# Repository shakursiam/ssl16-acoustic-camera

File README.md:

# SSL-16 — 16-Channel Acoustic Sound Source Localization Board (Lab Prototype, Rev A)

The **SSL-16** is an integrated 16-channel acoustic camera system engineered for real-time sound source localization (SSL) and acoustic beamforming, designed for downward-looking deployment to localize vehicle honking and characterize acoustic profiles in dense urban traffic environments (such as Dhaka, Bangladesh). The hardware integrates **16 Infineon IM73A135 differential analog MEMS microphones** arranged in a non-uniform Vogel (sunflower) spiral layout within an 80 mm radius aperture ($D = 160\,\text{mm}$), digitized synchronously by **four Texas Instruments TLV320ADC5140 4-channel ADCs** over a shared, daisy-chained 16-channel TDM bus into an **Espressif ESP32-S3-WROOM-1-N8R8** dual-core microcontroller with 8 MB Octal PSRAM.

---

## 3D Renders (Rev A)

<p align="center">
  <em>Figure 1: (Left) Top acoustic face with 16 sunflower sound entry ports. (Right) Bottom surface hosting all SMD components, differential routing, and ground flood.</em>
</p>

---

## Key Specifications

| Parameter | Specification / Value | Notes |
|---|---|---|
| **Microphone Array** | 16 × Infineon IM73A135V01XTSA1 (`MK1`–`MK16`) | Analog, differential, bottom-port, 73 dB(A) SNR, 135 dB SPL AOP |
| **Array Geometry** | Vogel / Sunflower spiral ($R = 80\,\text{mm}$ aperture) | Eliminates spatial aliasing up to 6 kHz; bottom-port through 0.8 mm NPTH holes |
| **Audio ADCs** | 4 × TI TLV320ADC5140 (`U1`–`U4`) | 4 differential analog inputs each; QFN-24 with 9 thermal vias per pad |
| **Sample Format** | TDM, 16 slots × 16 bits, $f_s = 48\,\text{kHz}$ | $\text{BCLK} = 12.288\,\text{MHz}$ (256 BCLK cycles per frame) |
| **Master Clock (MCLK)** | 24.576 MHz 3.3V CMOS XO (Abracon ASE-24.576MHZ-LC-T, `Y1`) | Directly feeds `U4` (`GPIO1`); `U4` acts as sole TDM Controller |
| **Clock Fan-Out Buffer** | TI LMK1C1104 (`U10`), 1:4 LVCMOS Buffer | Skew $< 30\,\text{ps}$; buffered BCLK feeds `U1`–`U3` and ESP32 `IO6` via 33 Ω damping resistors |
| **Microcontroller (MCU)**| ESP32-S3-WROOM-1-N8R8 (`U5`) | Dual-core Xtensa LX7 @ 240 MHz, 8 MB Flash, 8 MB Octal PSRAM, native USB-Serial/JTAG |
| **External Storage** | MicroSD socket (Molex 104031-0811, `J601`) | Native 4-bit SDMMC bus (`IO4`, `IO5`, `IO15`, `IO16`, `IO18`, `IO21`) |
| **Power Inputs** | 12 V DC barrel jack (`J8`) or USB-C 5 V (`J2`) | Automatic ideal-diode OR-ing ($Q_1$ P-MOSFET + $D_1$ Schottky) into `VSYS` |
| **Power Regulators** | XL2596S-5.0 (5V buck), AP2112K-3.3 (3V3 digital), TPS7A2033 (3V3A clean analog) | Unified continuous GND plane (no split analog ground) |
| **PCB Dimensions** | 230 mm × 170 mm, 4 layers, 1.6 mm nominal thickness | Stack-up: **JLCPCB JLC04161H-7628**; all 193 SMD components on bottom side |
| **Usable Acoustic Band**| **~1.5 kHz to 6.0 kHz** | Broad mainlobe below 1.5 kHz; zero grating lobes up to 6.0 kHz |

---

## System Architecture

```mermaid
flowchart TD
    subgraph FrontEnd ["Acoustic Array & Transducers"]
        direction LR
        MIC1["MK2, MK7, MK10, MK15<br/>(4× IM73A135 Diff)"]
        MIC2["MK1, MK4, MK9, MK12<br/>(4× IM73A135 Diff)"]
        MIC3["MK3, MK6, MK11, MK14<br/>(4× IM73A135 Diff)"]
        MIC4["MK5, MK8, MK13, MK16<br/>(4× IM73A135 Diff)"]
    end

    subgraph MasterClock ["Master Clock Source"]
        Y1["Abracon 24.576 MHz XO<br/>(ASE-24.576MHZ-LC-T)"]
        R22["R22 (33 Ω)"]
        Y1 --> R22
    end

    subgraph ADCs ["TDM Digitization & Daisy-Chain (4× TLV320ADC5140)"]
        U4["ADC-4 (U4, 0x4F)<br/><b>TDM Controller</b><br/>Slots 12–15"]
        U3["ADC-3 (U3, 0x4E)<br/>Target / Daisy In<br/>Slots 8–11"]
        U2["ADC-2 (U2, 0x4D)<br/>Target / Daisy In<br/>Slots 4–7"]
        U1["ADC-1 (U1, 0x4C)<br/>Target / Daisy Out<br/>Slots 0–3"]
    end

    subgraph ClockFanout ["Clock Fan-Out & Routing"]
        U10["LMK1C1104 (U10)<br/>1:4 LVCMOS Buffer"]
        R27["R27 (33 Ω)"]
        R13["R13 (33 Ω)"]
        R14["R14 (33 Ω)"]
        R15["R15 (33 Ω)"]
        R16["R16 (33 Ω)"]
        R28["R28 (33 Ω)"]
        TERM["R30 (51 Ω) + C54 (100 pF)<br/>AC End Termination"]
    end

    subgraph MCU ["Processing & Connectivity"]
        U5["ESP32-S3-WROOM-1-N8R8 (U5)<br/>I2S/TDM Slave, Wi-Fi 4, BLE 5"]
        SD["microSD Card (J601)<br/>4-Bit SDMMC"]
        USB["USB-C (J2)<br/>Native USB CDC / JTAG"]
        TMP["TMP112 (U9, 0x48)<br/>Thermal Sensor"]
        U5 --- SD
        U5 --- USB
    end

    %% Audio Analog Connections
    MIC4 -->|"4x Diff Pairs"| U4
    MIC3 -->|"4x Diff Pairs"| U3
    MIC2 -->|"4x Diff Pairs"| U2
    MIC1 -->|"4x Diff Pairs"| U1

    %% Clocks
    R22 -->|"MCLK (24.576 MHz)"| U4
    U4 -->|"BCLK (12.288 MHz)"| R27
    R27 --> U10
    U10 -->|"Y0"| R13
    R13 --> U1
    U10 -->|"Y1"| R14
    R14 --> U2
    U10 -->|"Y2"| R15
    R15 --> U3
    U10 -->|"Y3"| R16
    R16 -->|"IO6 (BCLK)"| U5

    %% FSYNC Fly-by
    U4 -->|"FSYNC (48 kHz)"| R28
    R28 --> U3
    U3 --> U2
    U2 --> U1
    U1 -->|"IO7 (FSYNC)"| U5
    U5 --- TERM

    %% Data Daisy-Chain
    U4 -->|"SDOUT via R26"| U3
    U3 -->|"SDOUT via R25"| U2
    U2 -->|"SDOUT via R23"| U1
    U1 -->|"SDOUT via R24 / I2S_DIN"| U5

    %% I2C & Control
    U5 -->|"IO8 SDA / IO9 SCL (2.2 kOhm Pull-ups)"| U1
    U5 -.->|"I2C"| U2
    U5 -.->|"I2C"| U3
    U5 -.->|"I2C"| U4
    U5 -.->|"I2C"| TMP
    U5 -->|"IO11 SHDNZ (100 kOhm Pull-down)"| U1
    U5 -.->|"SHDNZ"| U2
    U5 -.->|"SHDNZ"| U3
    U5 -.->|"SHDNZ"| U4
```

---

## Repository Structure

```
ssl16-acoustic-camera/
├── README.md                           ← Main repository documentation & overview
├── .gitignore                          ← KiCad temporary files and OS artifacts filter
├── .gitattributes                      ← Git LFS configuration for PDFs, images, renders
├── hardware/
│   ├── kicad/                          ← Complete KiCad 10 project source files
│   │   ├── Beamfoarming_16x.kicad_pro  ← KiCad project descriptor
│   │   ├── Beamfoarming_16x.kicad_pcb  ← 4-layer PCB layout (230 × 170 mm)
│   │   ├── Beamfoarming_16x.kicad_sch  ← Hierarchical schematic top sheet
│   │   ├── Beamfoarming_16x.kicad_dru  ← Custom design rule constraints
│   │   ├── Block_diagram.kicad_sch     ← Schematic: System block diagram
│   │   ├── MCU_sch.kicad_sch           ← Schematic: ESP32-S3, power regulators, USB
│   │   ├── adc_1.kicad_sch..adc_4.sch  ← Schematic: TLV320ADC5140 ADC sheets
│   │   ├── tdm.kicad_sch               ← Schematic: Clock buffer & TDM daisy-chain
│   │   ├── sdcard.kicad_sch            ← Schematic: MicroSD socket & activity LED
│   │   ├── MIC_ADC.kicad_sch, etc.     ← Schematic: Microphone coupling sheets
│   │   ├── fp-lib-table, sym-lib-table ← Library tables with portable ${KIPRJMOD} paths
│   │   └── Library_BeamForming/        ← Custom symbols, footprints, and 3D models
│   ├── fabrication/
│   │   └── rev_A/
│   │       ├── gerbers/                ← Exact Gerber & drill files sent to JLCPCB (29-10-2026)
│   │       ├── assembly/               ← JLCPCB BOM (xlsx/csv) and CPL pick-and-place files
│   │       └── README.md               ← Complete JLCPCB fab settings & order notes
│   └── exports/
│       ├── SSL16_RevA_schematic.pdf    ← Full hierarchical schematic export
│       ├── SSL16_RevA_pcb_layers.pdf   ← Individual PCB layer artwork plots
│       ├── drc_report.txt              ← KiCad DRC verification report
│       ├── erc_report.txt              ← KiCad ERC verification report
│       └── renders/                    ← Raytraced 3D renders (top & bottom views)
├── docs/                               ← Comprehensive engineering documentation
│   ├── architecture.md                 ← System architecture & block diagram
│   ├── clocking_and_tdm.md             ← Clock tree, timing margin, and TDM protocol
│   ├── adc_configuration.md            ← TLV320ADC5140 register map & MICBIAS warning
│   ├── microphone_array.md             ← Sunflower array coordinates & acoustic band
│   ├── power.md                        ← Dual-input PDN, ideal diode, and voltage rails
│   ├── pcb_stackup_and_rules.md        ← JLC04161H-7628 stack-up & 50 Ω coplanar rules
│   ├── esp32_pinout.md                 ← Comprehensive GPIO pinout & PSRAM conflict note
│   ├── bringup_checklist.md            ← 8-stage electrical & acoustic bring-up guide
│   ├── known_issues_and_todo.md        ← Rev A observations & Rev B roadmap
│   ├── design_review_log.md            ← Design decision log & engineering changes
│   └── images/                         ← Documentation graphics & diagrams
└── firmware/
    └── README.md                       ← ESP-IDF / Arduino I2S TDM slave driver notes
```

---

## How to Open and Work with the KiCad Project

1. **Software Requirement:** **KiCad 10.0.x** or later.
2. **Opening the Project:**
   - Launch KiCad and open [`hardware/kicad/Beamfoarming_16x.kicad_pro`](file:///h:/My%20Drive/Research_2026/Sound%20Source%20Localizaton/Project/System_Dev/ssl16-acoustic-camera/hardware/kicad/Beamfoarming_16x.kicad_pro).
3. **Library Management:**
   - All custom footprints and schematic symbols are bundled locally inside [`hardware/kicad/Library_BeamForming/`](file:///h:/My%20Drive/Research_2026/Sound%20Source%20Localizaton/Project/System_Dev/ssl16-acoustic-camera/hardware/kicad/Library_BeamForming/).
   - Both `fp-lib-table` and `sym-lib-table` utilize the portable `${KIPRJMOD}` environment variable. The project will open cleanly without broken references or missing libraries on any operating system.

---

## Fabrication & Assembly Summary

- **Manufacturer:** JLCPCB
- **Order Date:** October 2026
- **Stack-Up:** 4 Layers, 1.6 mm thickness, FR-4, **JLC04161H-7628** (outer 1 oz, inner 0.5 oz).
- **Surface Finish:** LeadFree HASL / ENIG; 0.2 mm plugged vias.
- **SMT Placements:** 193 placements (Bottom side only).
- **Production Files:**
  - Complete Gerbers: [`hardware/fabrication/rev_A/gerbers/`](file:///h:/My%20Drive/Research_2026/Sound%20Source%20Localizaton/Project/System_Dev/ssl16-acoustic-camera/hardware/fabrication/rev_A/gerbers/)
  - BOM & CPL: [`hardware/fabrication/rev_A/assembly/`](file:///h:/My%20Drive/Research_2026/Sound%20Source%20Localizaton/Project/System_Dev/ssl16-acoustic-camera/hardware/fabrication/rev_A/assembly/)
  - Order parameters & alignment remarks: [`hardware/fabrication/rev_A/README.md`](file:///h:/My%20Drive/Research_2026/Sound%20Source%20Localizaton/Project/System_Dev/ssl16-acoustic-camera/hardware/fabrication/rev_A/README.md)

---

## Documentation Index

Detailed engineering documentation is organized inside [`docs/`](file:///h:/My%20Drive/Research_2026/Sound%20Source%20Localizaton/Project/System_Dev/ssl16-acoustic-camera/docs/):

1. [**System Architecture & Block Diagram**](docs/architecture.md): High-level system structure, TDM controller concept, and clock distribution.
2. [**Clocking & TDM Bus Architecture**](docs/clocking_and_tdm.md): Master clock tree, 12.288 MHz distribution, timing margins, and transmission line damping.
3. [**ADC Configuration & Register Map**](docs/adc_configuration.md): TLV320ADC5140 initialization scripts, daisy-chain timing, and MICBIAS safety limits.
4. [**Sunflower Microphone Array**](docs/microphone_array.md): Vogel spiral geometry, exact coordinates (mm), acoustic bandwidth (1.5–6 kHz), and port keep-outs.
5. [**Power Delivery Network (PDN)**](docs/power.md): Dual-input 12V/USB power architecture, ideal-diode OR-ing, LDO regulation, and unified ground plane.
6. [**PCB Stack-Up & Design Rules**](docs/pcb_stackup_and_rules.md): JLC04161H-7628 layer stack, 50 Ω coplanar waveguides, differential pair rules, and keep-outs.
7. [**ESP32-S3 Pinout & Interface Mapping**](docs/esp32_pinout.md): Complete MCU pinout table, peripheral assignments, and Octal PSRAM GPIO35–37 advisory.
8. [**Hardware Bring-Up Checklist**](docs/bringup_checklist.md): 8-stage electrical verification procedure from cold checks to beamforming tests.
9. [**Known Issues & Rev B Roadmap**](docs/known_issues_and_todo.md): Identified prototype errata, BOM substitutions, and optimizations for Revision B.
10. [**Hardware Design Review Log**](docs/design_review_log.md): Record of design modifications and engineering decisions resolved during development.
11. [**Firmware Notes**](firmware/README.md): ESP-IDF and Arduino driver implementation notes and DMA configuration.

---

## Project Status

**Current Status:** **Rev A ordered from JLCPCB (Oct 2026), bring-up pending.**

---

## Authors & Affiliation

**Designers:**  
- **MD Abdus Shakur Siam** ([@shakursiam](https://github.com/shakursiam))  
- **Sadaf Shafin**  
- **Ashir Intesher**  

**Research Laboratory:**  
**HIVE (Hydrogen, Intelligent Vehicles & Energy) Research Group**  
Department of Electrical and Electronic Engineering (EEE)  
**Bangladesh University of Engineering and Technology (BUET)**, Dhaka, Bangladesh  

---

## Intellectual Property Notice

*All rights reserved – contact the authors for academic or commercial use. This repository contains unpublished research hardware.*

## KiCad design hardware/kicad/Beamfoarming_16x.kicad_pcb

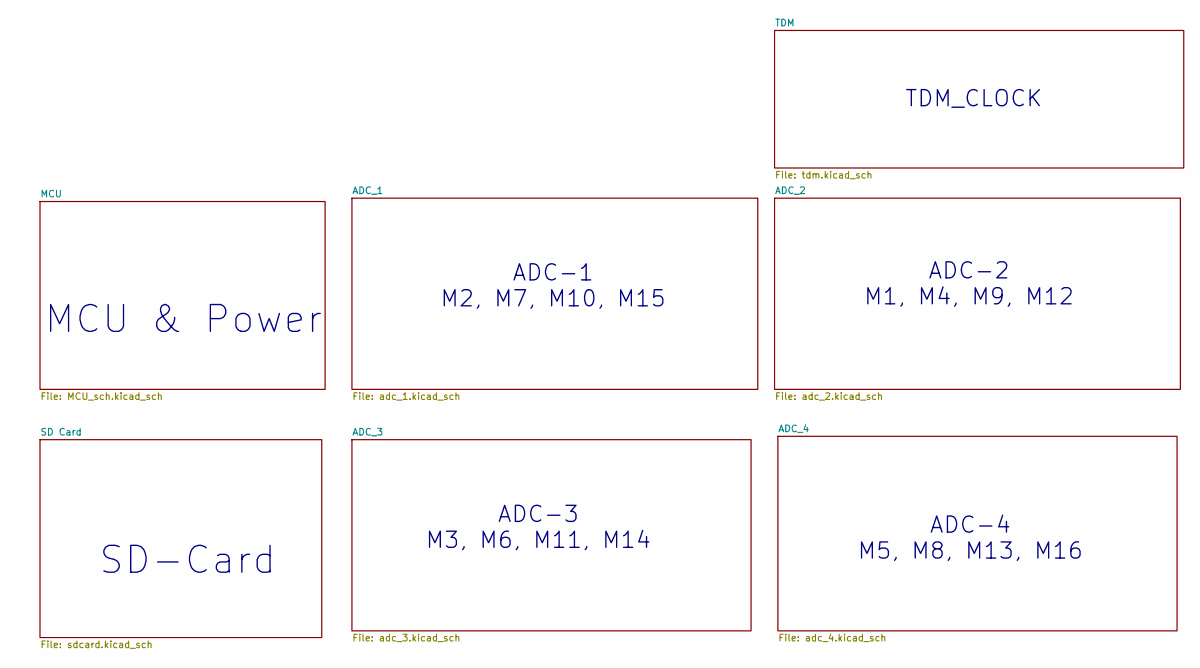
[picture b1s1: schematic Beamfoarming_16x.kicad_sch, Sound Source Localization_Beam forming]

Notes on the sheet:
ADC-4 M5, M8, M13, M16
ADC-3 M3, M6, M11, M14
ADC-2 M1, M4, M9, M12
TDM_CLOCK
SD-Card
ADC-1 M2, M7, M10, M15
MCU & Power

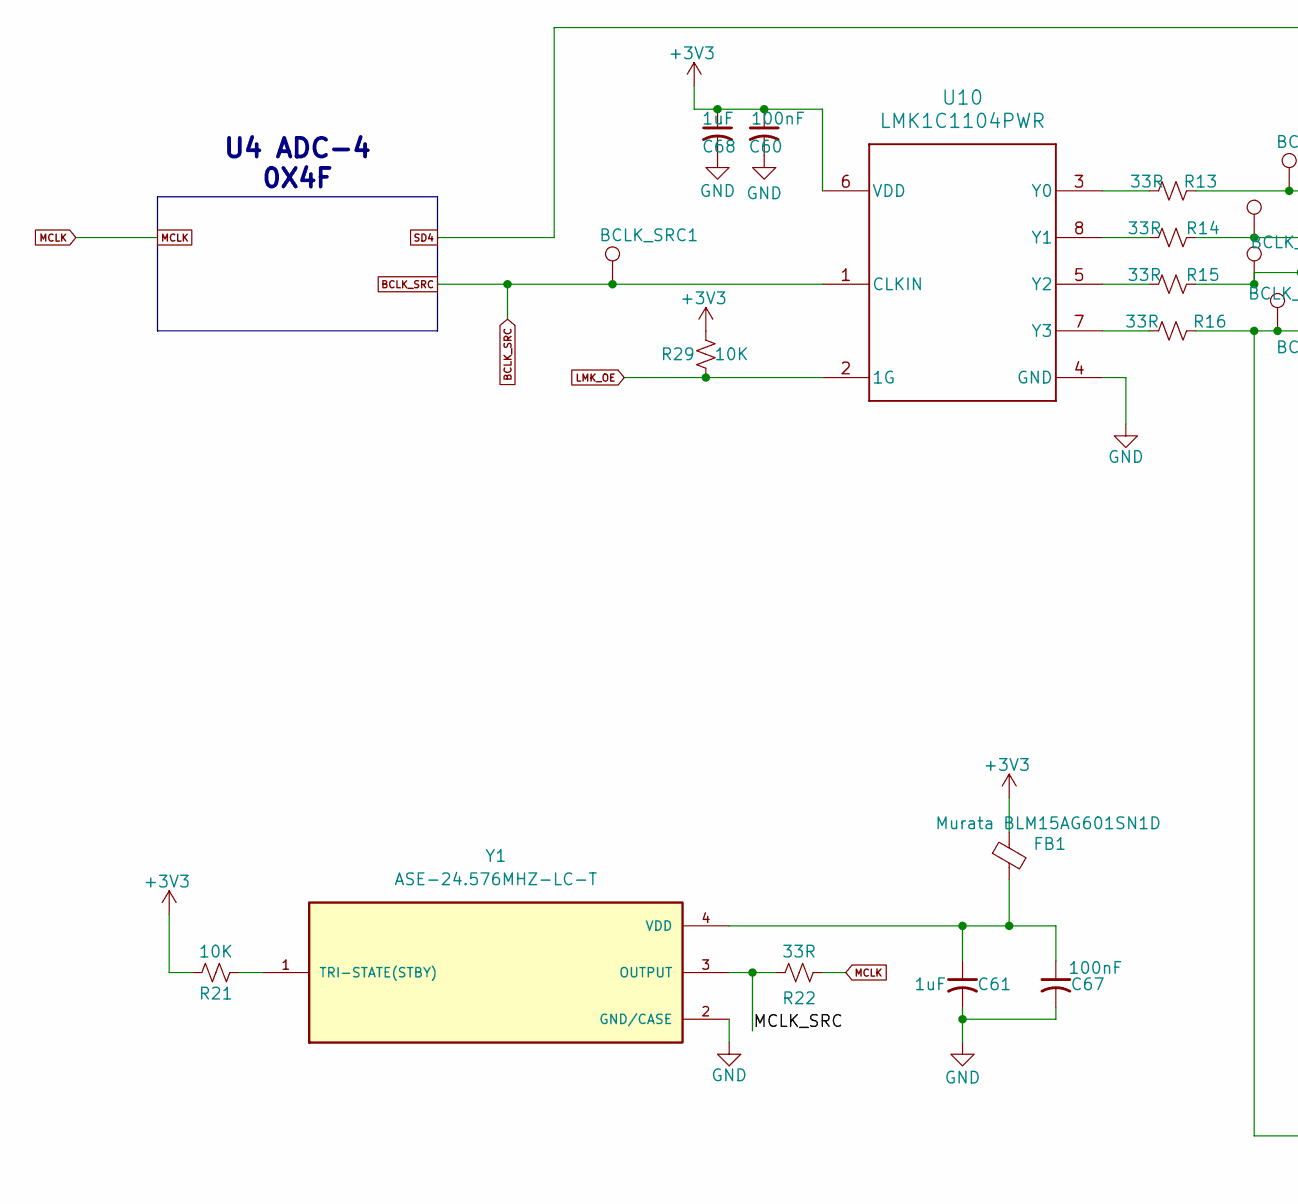
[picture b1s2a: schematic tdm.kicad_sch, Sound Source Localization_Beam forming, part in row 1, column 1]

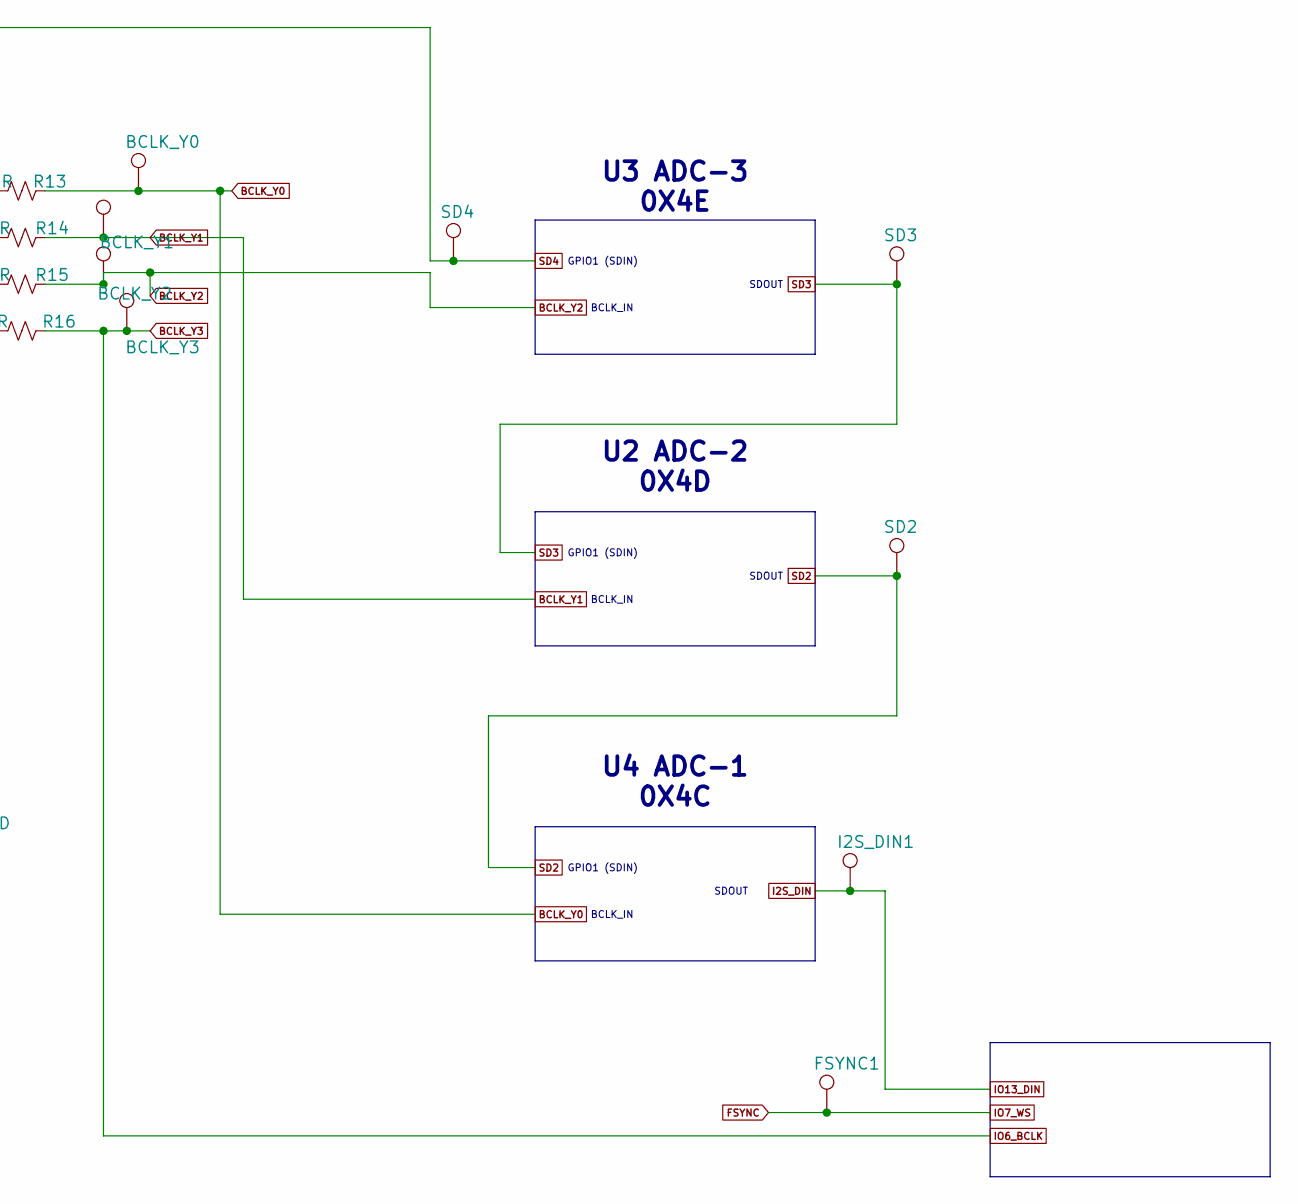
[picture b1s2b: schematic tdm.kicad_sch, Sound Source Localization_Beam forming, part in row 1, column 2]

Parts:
BCLK_SRC1: TestPoint; TestPoint_Pad_D1.5mm
BCLK_Y0, BCLK_Y1, BCLK_Y2, BCLK_Y3: TestPoint; TestPoint_Pad_D1.5mm
C60, C67: 100nF; C_0402_1005Metric
C61, C68: 1uF; C_0402_1005Metric
FB1: Murata BLM15AG601SN1D; BEADC1005X55N
FSYNC1: TestPoint; TestPoint_Pad_D1.5mm
I2S_DIN1: TestPoint; TestPoint_Pad_D1.5mm
R13, R14, R15, R16, R22: 33R; R_0402_1005Metric
R21, R29: 10K; R_0402_1005Metric
SD2, SD3, SD4: TestPoint; TestPoint_Pad_D1.5mm
U10: LMK1C1104PWR; PW0008A-IPC_A
Y1: ASE-24.576MHZ-LC-T; XTAL_ASE-24.576MHZ-LC-T; PARTREV 02-18-22

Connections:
+3V3: C60.1, C68.1, FB1.1, R21.2, R29.1, U10.6 (VDD); also elsewhere on the board
/TDM/MCLK_SRC: R22.2, Y1.3 (OUTPUT)
BCLK_SRC: BCLK_SRC1.1 (1_1), U10.1 (CLKIN); also elsewhere on the board
BCLK_Y0: BCLK_Y0.1 (1_1), R13.1; also elsewhere on the board
BCLK_Y1: BCLK_Y1.1 (1_1), R14.1; also elsewhere on the board
BCLK_Y2: BCLK_Y2.1 (1_1), R15.1; also elsewhere on the board
BCLK_Y3: BCLK_Y3.1 (1_1), R16.1; also elsewhere on the board
FSYNC: FSYNC1.1 (1_1); also elsewhere on the board
GND: C60.2, C61.2, C67.2, C68.2, U10.4 (GND), Y1.2 (GND/CASE); also elsewhere on the board
I2S_DIN: I2S_DIN1.1 (1_1); also elsewhere on the board
LMK_OE: R29.2, U10.2 (1G)
MCLK: R22.1; also elsewhere on the board
unnamed: R13.2, U10.3 (Y0)
unnamed: R14.2, U10.8 (Y1)
unnamed: R15.2, U10.5 (Y2)
unnamed: R16.2, U10.7 (Y3)
unnamed: R21.1, Y1.1 (TRI-STATE(STBY))
unnamed: C61.1, C67.1, FB1.2, Y1.4 (VDD)
SD2: SD2.1 (1_1); also elsewhere on the board
SD3: SD3.1 (1_1); also elsewhere on the board
SD4: SD4.1 (1_1); also elsewhere on the board

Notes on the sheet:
BCLK_IN
GPIO1 (SDIN)
U4 ADC-1 0X4C
SDOUT
U4 ADC-4 0X4F
U2 ADC-2 0X4D
U3 ADC-3 0X4E

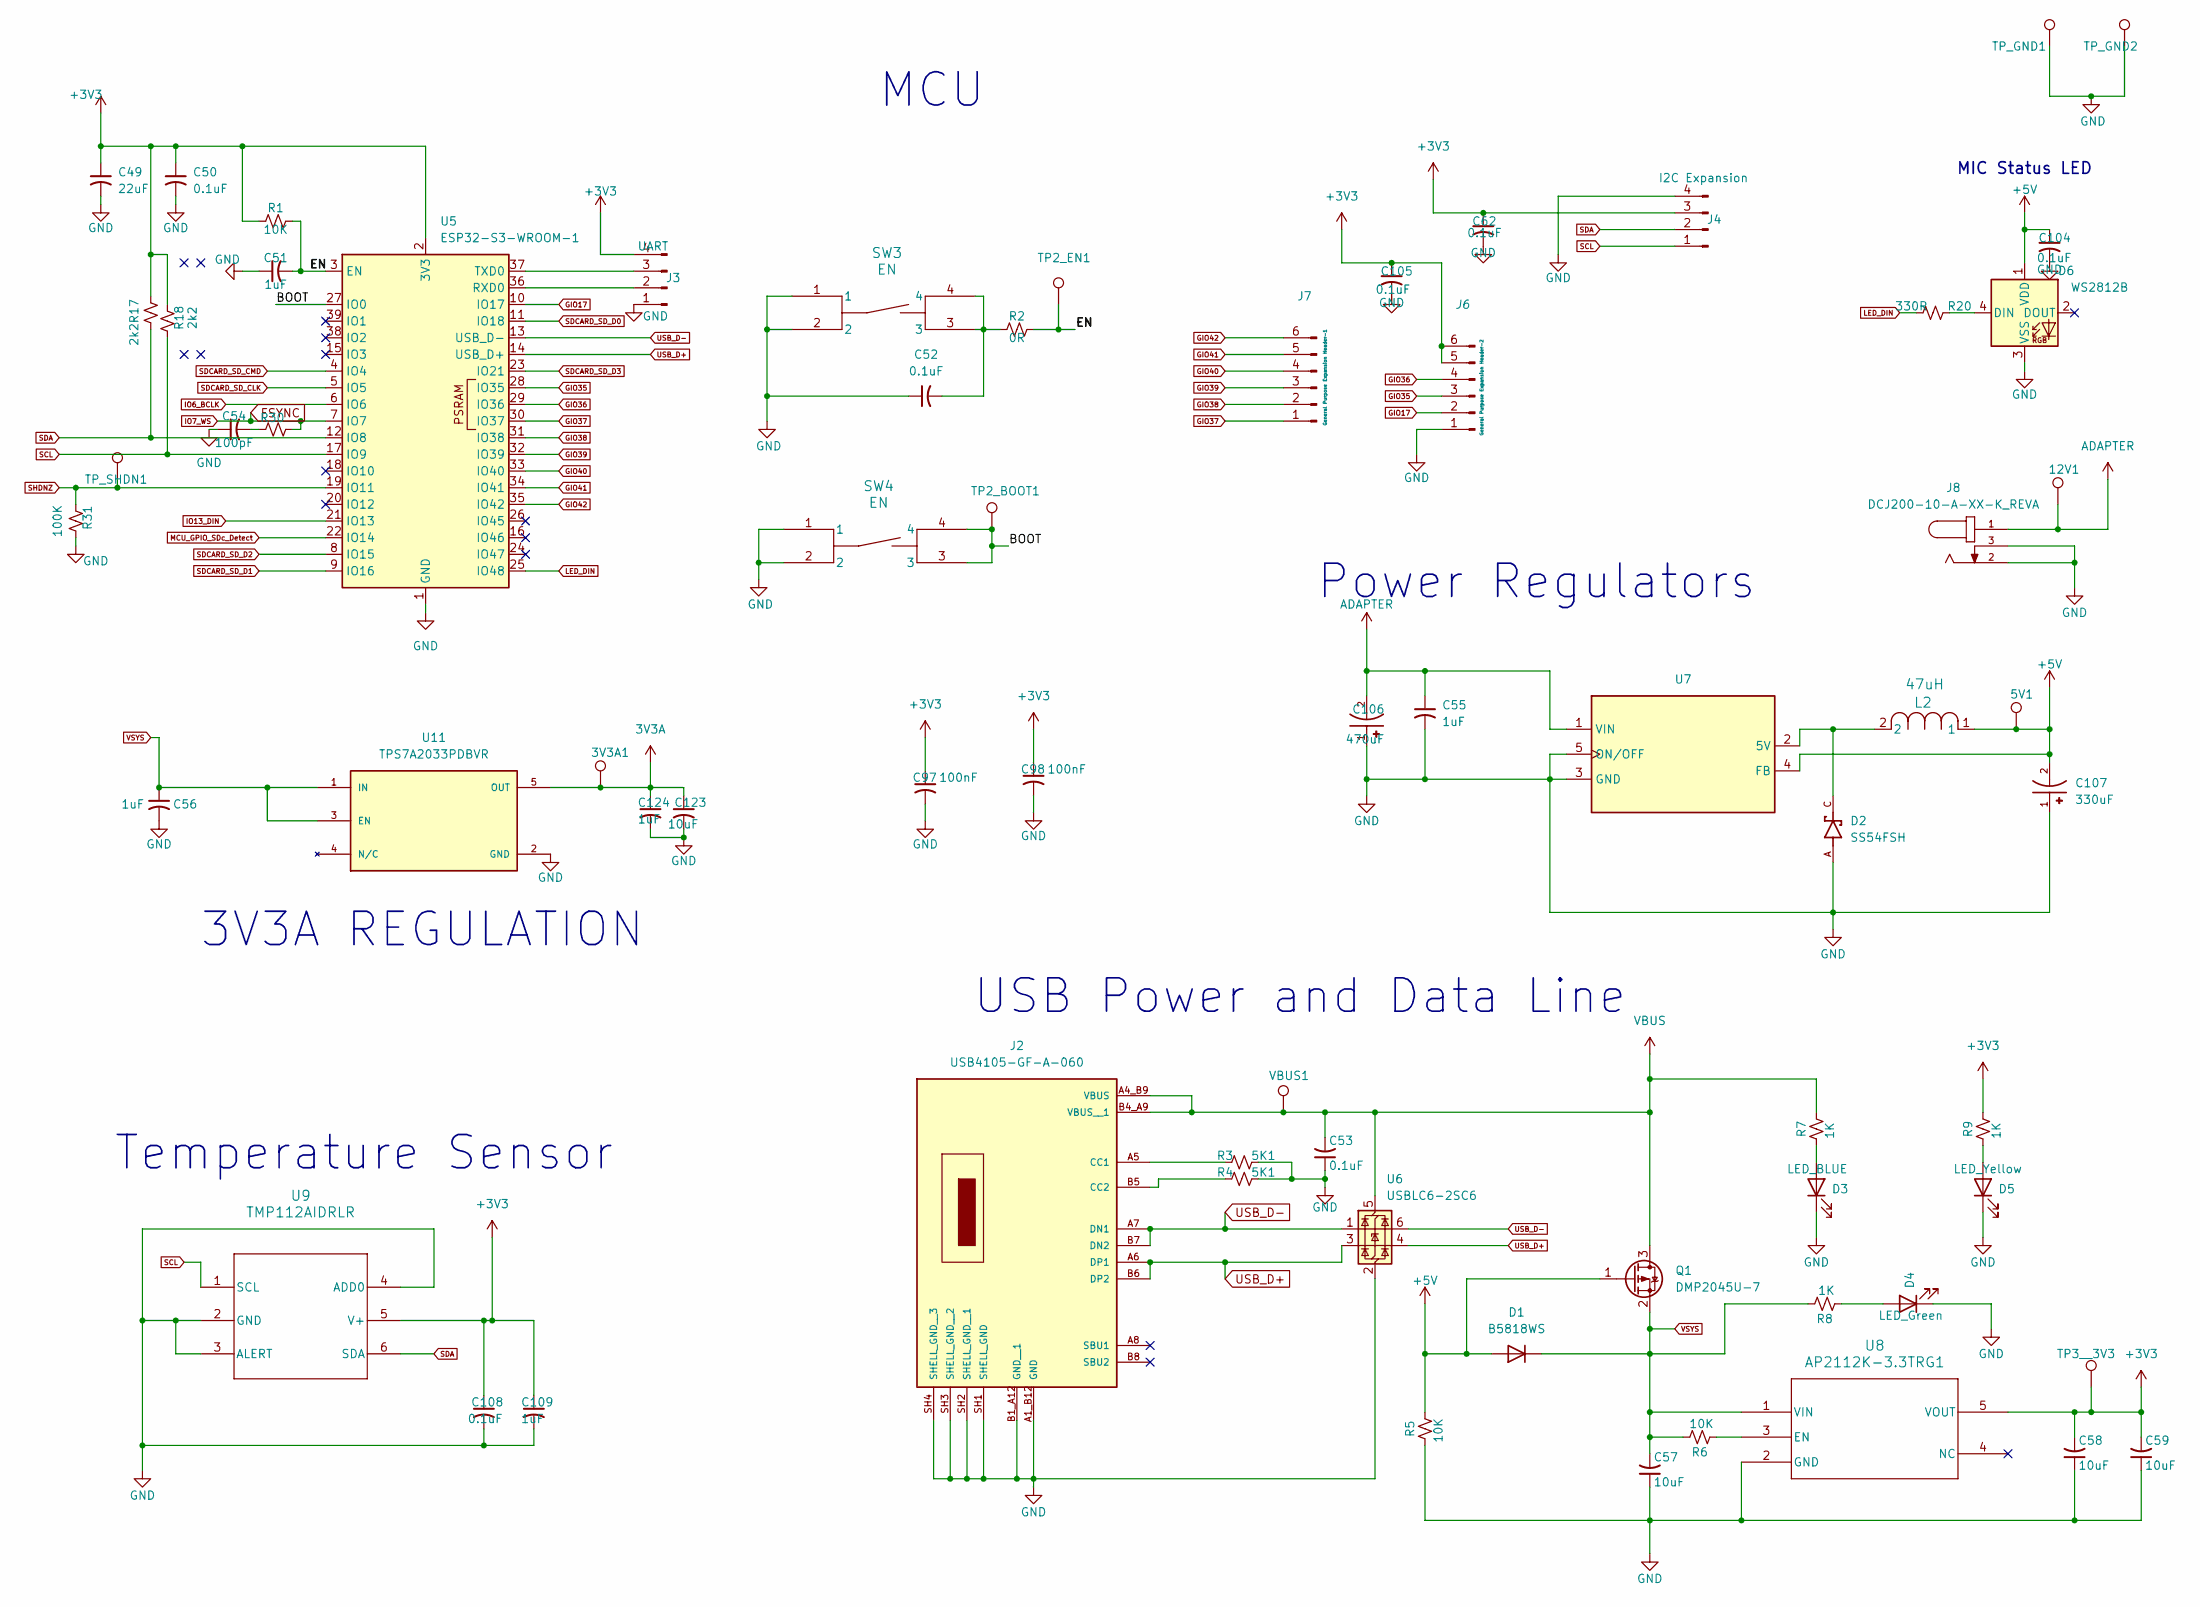
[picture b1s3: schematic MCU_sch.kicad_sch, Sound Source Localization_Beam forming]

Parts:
3V3A1: TestPoint; TestPoint_Plated_Hole_D2.0mm
5V1: TestPoint_Plated_Hole_D2.0mm
12V1: TestPoint; TestPoint_Plated_Hole_D3.0mm
C49: 22uF; C_1206_3216Metric
C50, C52, C53, C62, C104, C105, C108: 0.1uF; C_0402_1005Metric
C51, C109, C124: 1uF; C_0402_1005Metric
C54: 100pF; C_0402_1005Metric
C55, C56: 1uF; C_1206_3216Metric
C57, C58, C59: 10uF; C_0603_1608Metric
C97, C98: 100nF; C_0402_1005Metric
C106: 470uF; CAP_EEEFK1V471AQ; PARTREV 10-Oct-19
C107: 330uF; CAP_EEEFK1V471AQ; PARTREV 10-Oct-19
C123: 10uF; C_0805_2012Metric_Pad1.18x1.45mm_HandSolder
D1: B5818WS; D_SOD-323
D2: SS54FSH; SODFL4725X110N; PARTREV B2103
D3: LED_BLUE; LED_0603_1608Metric
D4: LED_Green; LED_0603_1608Metric
D5: LED_Yellow; LED_0603_1608Metric
D6: WS2812B; LED_WS2812B_PLCC4_5.0x5.0mm_P3.2mm
J2: USB4105-GF-A-060; GCT_USB4105-GF-A-060; PARTREV B3
J3: UART; PinHeader_1x04_P2.00mm_Vertical
J4: I2C Expansion; PinHeader_1x04_P2.00mm_Vertical
J6: General Purpose Expansion Header-2; PinHeader_1x06_P2.00mm_Vertical
J7: General Purpose Expansion Header-1; PinHeader_1x06_P2.00mm_Vertical
J8: DCJ200-10-A-XX-K_REVA; GCT_DCJ200-10-A-XX-K_REVA; PARTREV A
L2: 47uH; IND_AMRM00101040_PUL
Q1: DMP2045U-7; SOT-23
R1, R5, R6: 10K; R_0402_1005Metric
R2: 0R; R_0402_1005Metric
R3, R4: 5K1; R_0402_1005Metric
R7, R8, R9: 1K; R_0402_1005Metric
R17, R18: 2k2; R_0402_1005Metric
R20: 330R; R_0402_1005Metric
R30: 51R; R_0402_1005Metric
R31: 100K; R_0402_1005Metric
SW3, SW4: EN; SON4_PTS526 SM15 SMTR2 LFS_CNK
TP2_BOOT1, TP3__3V3: TestPoint_Plated_Hole_D2.0mm
TP2_EN1: TestPoint_Pad_D1.5mm
TP_GND1, TP_GND2: TestPoint; TestPoint_Plated_Hole_D3.0mm
TP_SHDN1: TestPoint; TestPoint_Pad_D1.5mm
U5: ESP32-S3-WROOM-1
U6: USBLC6-2SC6; SOT-23-6
U7: 3A 150KHz 40V Buck DC to DC Converter; TO-263-5_TabPin3; LCSC Part Number C74190
U8: AP2112K-3.3TRG1; SOT_RG1_DIO
U9: TMP112AIDRLR; DRL0006A
U11: TPS7A2033PDBVR; SOT95P280X145-5N; PARTREV H
VBUS1: TestPoint_Plated_Hole_D2.0mm

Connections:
3V3A: 3V3A1.1 (1_1), C123.1, C124.1, U11.5 (OUT); also elsewhere on the board
+3V3: C49.1, C50.1, C58.2, C59.2, C62.1, C97.1, C98.1, C105.1, C108.1, C109.1, J3.4, J4.3, J6.5, J6.6, R1.1, R9.2, R17.2, R18.2, TP3__3V3.1, U5.2 (3V3), U8.5 (VOUT), U9.5 (V+); also elsewhere on the board
+5V: 5V1.1 (1_1), C104.1, C107.2, D1.2 (A), D6.1 (VDD), L2.1, Q1.1 (G), R5.2, U7.4 (FB)
/MCU/BOOT: SW4.3, SW4.4, TP2_BOOT1.1 (1_1), U5.27 (IO0)
/MCU/EN: C51.2, R1.2, R2.2, TP2_EN1.1 (1_1), U5.3 (EN)
ADAPTER: 12V1.1 (1_1), C55.1, C106.2, J8.1, U7.1 (VIN)
BCLK_Y3: U5.6 (IO6); also elsewhere on the board
FSYNC: R30.1, U5.7 (IO7); also elsewhere on the board
GIO17: J6.2, U5.10 (IO17)
GIO35: J6.3, U5.28 (IO35)
GIO36: J6.4, U5.29 (IO36)
GIO37: J7.1, U5.30 (IO37)
GIO38: J7.2, U5.31 (IO38)
GIO39: J7.3, U5.32 (IO39)
GIO40: J7.4, U5.33 (IO40)
GIO41: J7.5, U5.34 (IO41)
GIO42: J7.6, U5.35 (IO42)
GND: C49.2, C50.2, C51.1, C52.1, C53.1, C54.1, C55.2, C56.2, C57.1, C58.1, C59.1, C62.2, C97.2, C98.2, C104.2, C105.2, C106.1, C107.1, C108.2, C109.2, C123.2, C124.2, D2.A, D3.1 (K), D4.1 (K), D5.1 (K), D6.3 (VSS), J2.A1_B12 (GND), J2.B1_A12 (GND__1), J2.SH1 (SHELL_GND), J2.SH2 (SHELL_GND__1), J2.SH3 (SHELL_GND__2), J2.SH4 (SHELL_GND__3), J3.1, J4.4, J6.1, J8.2, J8.3, R3.2, R4.2, R5.1, R31.1, SW3.1, SW3.2, SW4.1, SW4.2, TP_GND1.1 (1_1), TP_GND2.1 (1_1), U5.1 (GND), U5.40 (GND), U5.41 (GND), U6.2 (GND), U7.3 (GND), U7.5 (ON/OFF), U8.2 (GND), U9.2 (GND), U9.3 (ALERT), U9.4 (ADD0), U11.2 (GND); also elsewhere on the board
I2S_DIN: U5.21 (IO13); also elsewhere on the board
LED_DIN: R20.2, U5.25 (IO48)
MCU_GPIO_SDc_Detect: U5.22 (IO14); also elsewhere on the board
unnamed: C52.2, R2.1, SW3.3, SW3.4
unnamed: C54.2, R30.2
unnamed: D3.2 (A), R7.1
unnamed: D4.2 (A), R8.1
unnamed: D5.2 (A), R9.1
unnamed: D6.4 (DIN), R20.1
unnamed: J2.A5 (CC1), R3.1
unnamed: J2.B5 (CC2), R4.1
unnamed: J3.2, U5.36 (RXD0)
unnamed: J3.3, U5.37 (TXD0)
unnamed: D2.C, L2.2, U7.2 (5V)
unnamed: R6.1, U8.3 (EN)
SCL: J4.1, R18.1, U5.17 (IO9), U9.1 (SCL); also elsewhere on the board
SDA: J4.2, R17.1, U5.12 (IO8), U9.6 (SDA); also elsewhere on the board
SDCARD_SD_CLK: U5.5 (IO5); also elsewhere on the board
SDCARD_SD_CMD: U5.4 (IO4); also elsewhere on the board
SDCARD_SD_D0: U5.11 (IO18); also elsewhere on the board
SDCARD_SD_D1: U5.9 (IO16); also elsewhere on the board
SDCARD_SD_D2: U5.8 (IO15); also elsewhere on the board
SDCARD_SD_D3: U5.23 (IO21); also elsewhere on the board
SHDNZ: R31.2, TP_SHDN1.1 (1_1), U5.19 (IO11); also elsewhere on the board
USB_D+: J2.A6 (DP1), J2.B6 (DP2), U5.14 (USB_D+), U6.3 (I/O2), U6.4 (I/O2)
USB_D-: J2.A7 (DN1), J2.B7 (DN2), U5.13 (USB_D-), U6.1 (I/O1), U6.6 (I/O1)
VBUS: C53.2, J2.A4_B9 (VBUS), J2.B4_A9 (VBUS__1), Q1.3 (D), R7.2, U6.5 (VBUS), VBUS1.1 (1_1)
VSYS: C56.1, C57.2, D1.1 (K), Q1.2 (S), R6.2, R8.2, U8.1 (VIN), U11.1 (IN), U11.3 (EN)

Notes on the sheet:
MCU
Power Regulators
USB Power and Data Line
MIC Status LED
Temperature Sensor
3V3A REGULATION

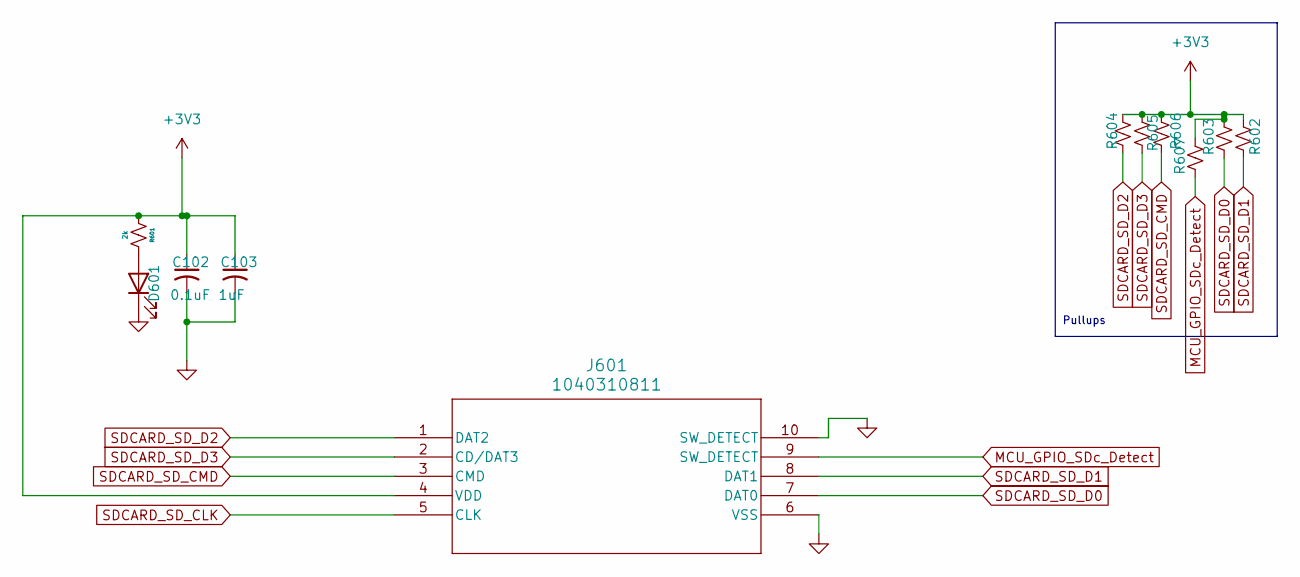
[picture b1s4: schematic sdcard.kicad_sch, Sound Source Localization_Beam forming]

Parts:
C102: 0.1uF; C_0603_1608Metric_Pad1.08x0.95mm_HandSolder
C103: 1uF; C_0603_1608Metric_Pad1.08x0.95mm_HandSolder
D601: LED; LED_0402_1005Metric_Pad0.77x0.64mm_HandSolder
J601: 1040310811; 104031-0811_MOL
R601: 2k; R_0402_1005Metric_Pad0.72x0.64mm_HandSolder
R602, R603, R605, R606, R607: 10K; R_0402_1005Metric_Pad0.72x0.64mm_HandSolder
R604: 10k; R_0402_1005Metric_Pad0.72x0.64mm_HandSolder

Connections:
+3V3: C102.1, C103.1, J601.4 (VDD), R601.1, R602.2, R603.2, R604.2, R605.2, R606.2, R607.2; also elsewhere on the board
GND: C102.2, C103.2, D601.1 (K), J601.6 (VSS), J601.10 (SW_DETECT), J601.11, J601.12, J601.13, J601.14; also elsewhere on the board
MCU_GPIO_SDc_Detect: J601.9 (SW_DETECT), R607.1; also elsewhere on the board
unnamed: D601.2 (A), R601.2
SDCARD_SD_CLK: J601.5 (CLK); also elsewhere on the board
SDCARD_SD_CMD: J601.3 (CMD), R606.1; also elsewhere on the board
SDCARD_SD_D0: J601.7 (DAT0), R603.1; also elsewhere on the board
SDCARD_SD_D1: J601.8 (DAT1), R602.1; also elsewhere on the board
SDCARD_SD_D2: J601.1 (DAT2), R604.1; also elsewhere on the board
SDCARD_SD_D3: J601.2 (CD/DAT3), R605.1; also elsewhere on the board

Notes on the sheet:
Pullups

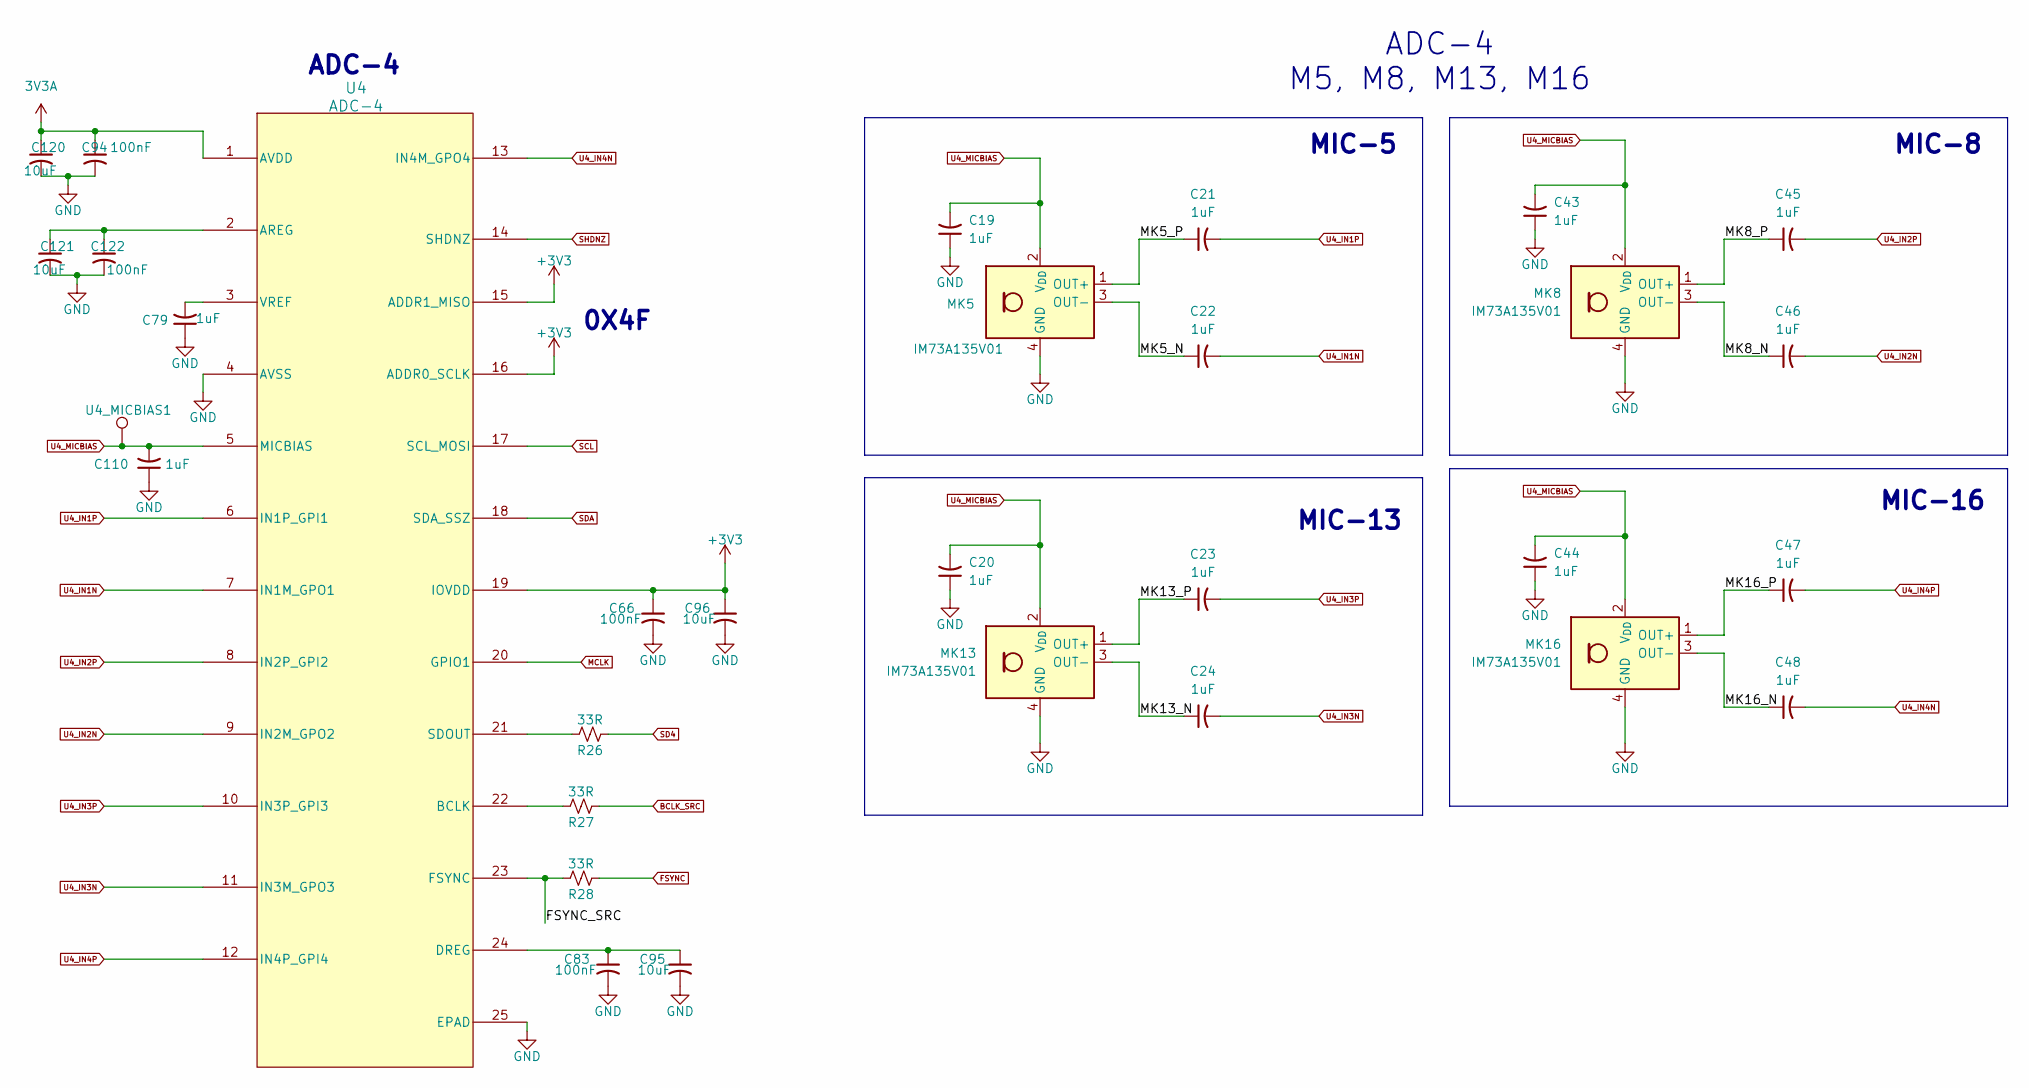
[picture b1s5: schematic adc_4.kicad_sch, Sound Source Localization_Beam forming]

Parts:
C19, C20, C21, C22, C23, C24, C43, C44, C45, C46, C47, C48, C79, C110: 1uF; C_0402_1005Metric
C66, C83, C94, C122: 100nF; C_0402_1005Metric
C95, C96, C120, C121: 10uF; C_0805_2012Metric_Pad1.18x1.45mm_HandSolder
MK5, MK8, MK13, MK16: IM73A135V01; Infineon_PG-LLGA-5-2
R26, R27, R28: 33R; R_0402_1005Metric
U4: ADC-4; RTW24_4P15X4P15_TEX
U4_MICBIAS1: TestPoint; TestPoint_Pad_D1.5mm

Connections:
3V3A: C94.1, C120.1, U4.1 (AVDD); also elsewhere on the board
+3V3: C66.1, C96.1, U4.15 (ADDR1_MISO), U4.16 (ADDR0_SCLK), U4.19 (IOVDD); also elsewhere on the board
/ADC_4/FSYNC_SRC: R28.2, U4.23 (FSYNC)
/ADC_4/MK5_N: C22.1, MK5.3 (OUT-)
/ADC_4/MK5_P: C21.1, MK5.1 (OUT+)
/ADC_4/MK8_N: C46.1, MK8.3 (OUT-)
/ADC_4/MK8_P: C45.1, MK8.1 (OUT+)
/ADC_4/MK13_N: C24.1, MK13.3 (OUT-)
/ADC_4/MK13_P: C23.1, MK13.1 (OUT+)
/ADC_4/MK16_N: C48.1, MK16.3 (OUT-)
/ADC_4/MK16_P: C47.1, MK16.1 (OUT+)
BCLK_SRC: R27.1; also elsewhere on the board
FSYNC: R28.1; also elsewhere on the board
GND: C19.1, C20.1, C43.1, C44.1, C66.2, C79.1, C83.2, C94.2, C95.2, C96.2, C110.1, C120.2, C121.2, C122.2, MK5.4 (GND), MK5.5 (GND), MK8.4 (GND), MK8.5 (GND), MK13.4 (GND), MK13.5 (GND), MK16.4 (GND), MK16.5 (GND), U4.4 (AVSS), U4.25 (EPAD); also elsewhere on the board
MCLK: U4.20 (GPIO1); also elsewhere on the board
unnamed: C121.1, C122.1, U4.2 (AREG)
unnamed: R27.2, U4.22 (BCLK)
unnamed: C83.1, C95.1, U4.24 (DREG)
unnamed: R26.2, U4.21 (SDOUT)
unnamed: C79.2, U4.3 (VREF)
SCL: U4.17 (SCL_MOSI); also elsewhere on the board
SD4: R26.1; also elsewhere on the board
SDA: U4.18 (SDA_SSZ); also elsewhere on the board
SHDNZ: U4.14 (SHDNZ); also elsewhere on the board
U4_IN1N: C22.2, U4.7 (IN1M_GPO1)
U4_IN1P: C21.2, U4.6 (IN1P_GPI1)
U4_IN2N: C46.2, U4.9 (IN2M_GPO2)
U4_IN2P: C45.2, U4.8 (IN2P_GPI2)
U4_IN3N: C24.2, U4.11 (IN3M_GPO3)
U4_IN3P: C23.2, U4.10 (IN3P_GPI3)
U4_IN4N: C48.2, U4.13 (IN4M_GPO4)
U4_IN4P: C47.2, U4.12 (IN4P_GPI4)
U4_MICBIAS: C19.2, C20.2, C43.2, C44.2, C110.2, MK5.2 (V_{DD}), MK8.2 (V_{DD}), MK13.2 (V_{DD}), MK16.2 (V_{DD}), U4.5 (MICBIAS), U4_MICBIAS1.1 (1_1)

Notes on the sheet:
ADC-4
MIC-16
MIC-13
ADC-4 M5, M8, M13, M16
MIC-5
MIC-8
0X4F
